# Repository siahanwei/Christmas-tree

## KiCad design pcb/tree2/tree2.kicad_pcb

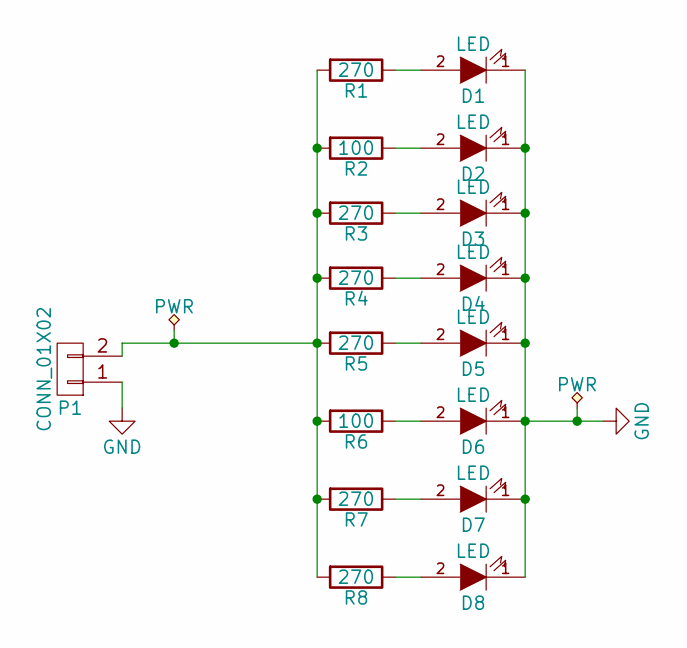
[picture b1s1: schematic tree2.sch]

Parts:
D1, D2, D3, D4, D5, D6, D7, D8: LED; 0805-LED
P1: CONN_01X02; M20_connector_hw
R1, R3, R4, R5, R7, R8: 270; 0805
R2, R6: 100; 0805

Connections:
GND: D1.1 (K), D2.1 (K), D3.1 (K), D4.1 (K), D5.1 (K), D6.1 (K), D7.1 (K), D8.1 (K), P1.1
unnamed: D1.2 (A), R1.1
unnamed: D2.2 (A), R2.1
unnamed: D3.2 (A), R3.1
unnamed: D4.2 (A), R4.1
unnamed: D5.2 (A), R5.1
unnamed: D6.2 (A), R6.1
unnamed: D7.2 (A), R7.1
unnamed: D8.2 (A), R8.1
unnamed: P1.2, R1.2, R2.2, R3.2, R4.2, R5.2, R6.2, R7.2, R8.2

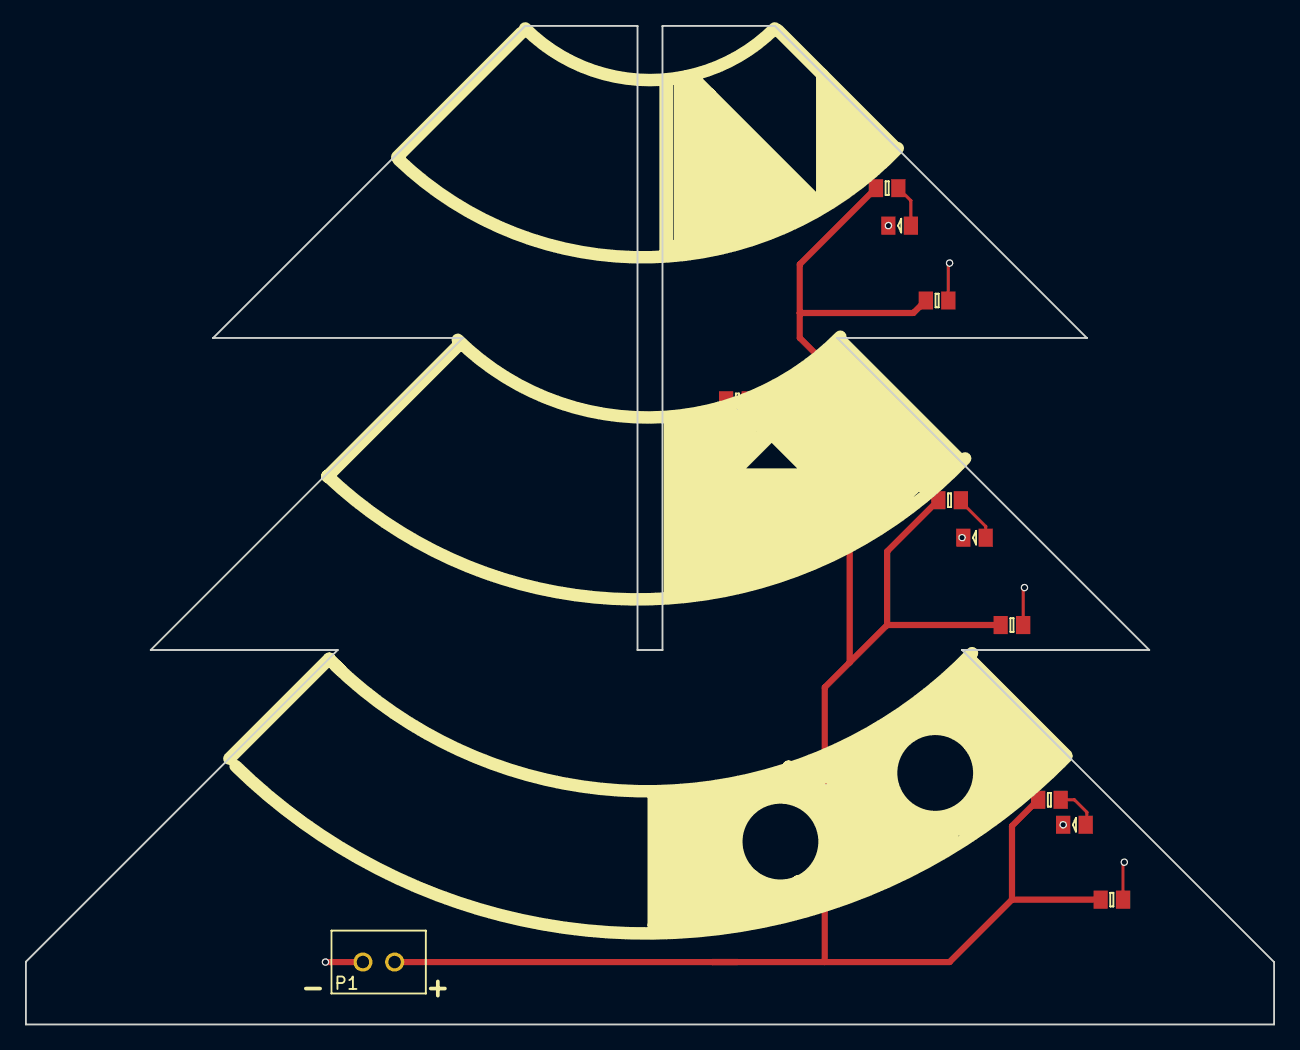
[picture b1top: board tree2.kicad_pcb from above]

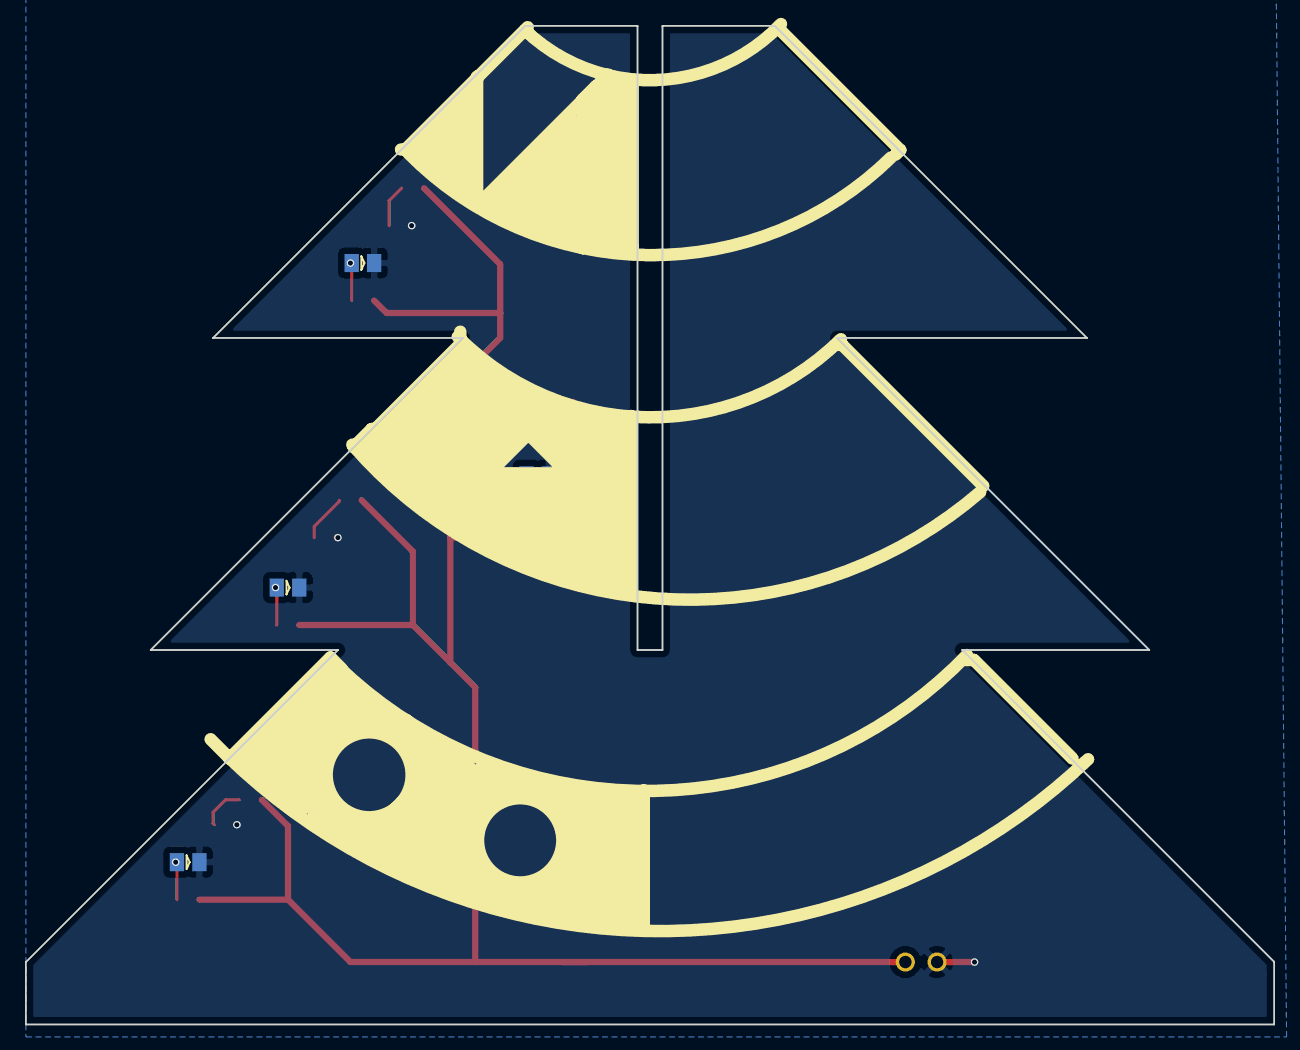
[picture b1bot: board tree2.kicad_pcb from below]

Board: 2 copper layers, 100.0 x 80.0 mm, 17 parts (4 on the bottom side), 10 nets.

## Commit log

2016-12-19 added asd.txt
2016-12-19 modified asd.txt
2016-12-19 deleted asd.txt
